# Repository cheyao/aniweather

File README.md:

<h1 align="center">Aniweather - Your personal anime weather station!</h1>

This is a 3D weather station! You can choose between displaying daily waifu pics and the current weather. **No external libraries used!**

Made for #asylum. The main API code is at https://github.com/cheyao/short with nest :D

To change the settings, edit `firmware/settings.h`! The weather info is mostly parsed on nest.

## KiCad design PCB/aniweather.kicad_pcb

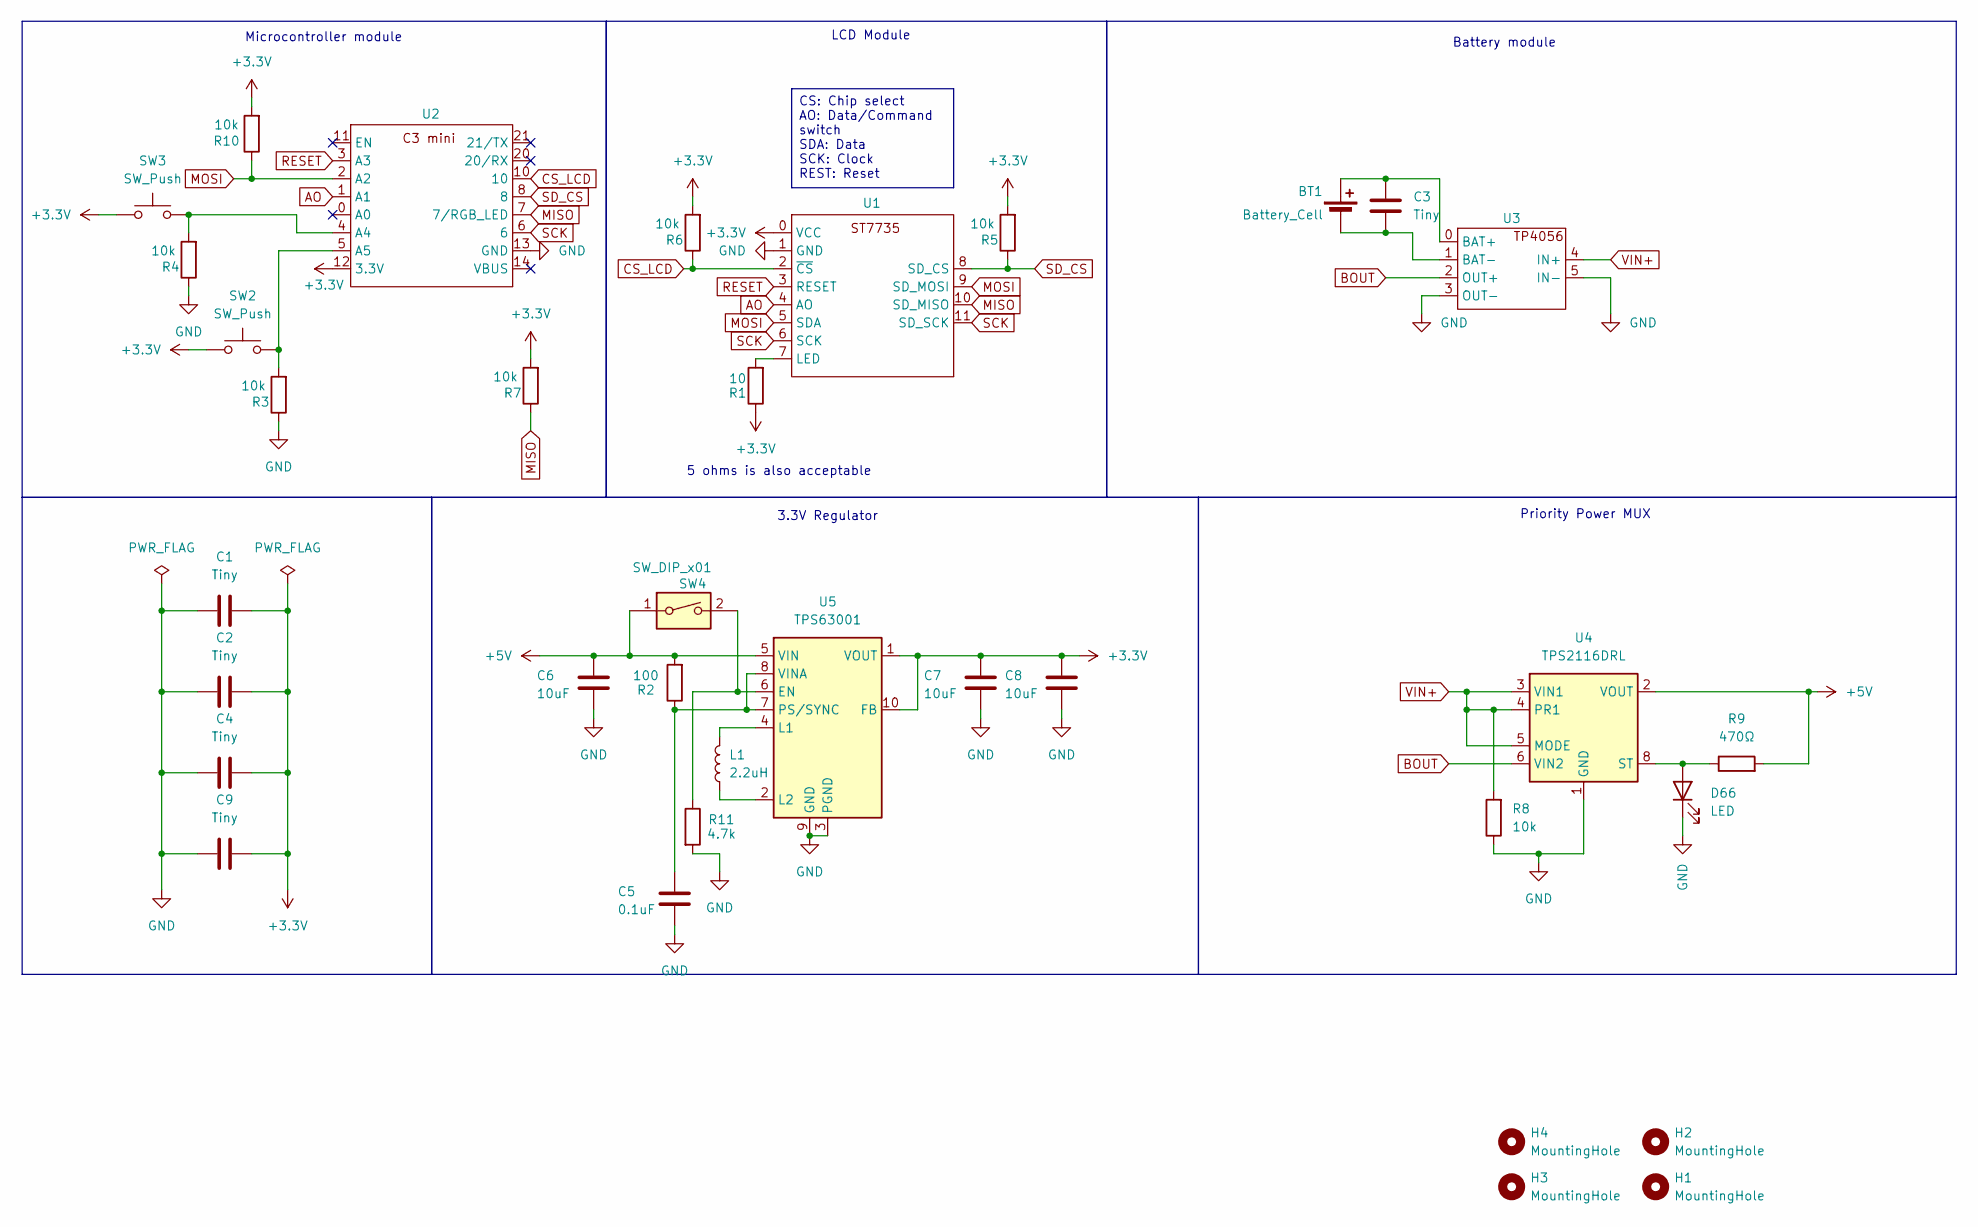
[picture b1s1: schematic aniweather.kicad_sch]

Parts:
BT1: Battery_Cell; TestPoint_2Pads_Pitch5.08mm_Drill1.3mm
C1, C2, C3, C4, C9: Tiny; C_0805_2012Metric_Pad1.18x1.45mm_HandSolder
C5: 0.1uF; C_0805_2012Metric_Pad1.18x1.45mm_HandSolder
C6, C7, C8: 10uF; C_0805_2012Metric_Pad1.18x1.45mm_HandSolder
D66: LED; LED_0603_1608Metric_Pad1.05x0.95mm_HandSolder
H1, H2, H3, H4: MountingHole; MountingHole_3.2mm_M3
L1: 2.2uH; NR3015T2R2M
R1: 10; R_0805_2012Metric_Pad1.20x1.40mm_HandSolder
R2: 100; R_0805_2012Metric_Pad1.20x1.40mm_HandSolder
R3, R4, R5, R6, R7, R8, R10: 10k; R_0805_2012Metric_Pad1.20x1.40mm_HandSolder
R9: 470Ω; R_0805_2012Metric_Pad1.20x1.40mm_HandSolder
R11: 4.7k; R_0805_2012Metric_Pad1.20x1.40mm_HandSolder
SW2, SW3: SW_Push; SW_PUSH_6mm
SW4: SW_DIP_x01; SW_DIP_SPSTx01_Slide_9.78x4.72mm_W7.62mm_P2.54mm
U1: ST7735
U2: WEMOS_C1_mini
U3: TP4056
U4: TPS2116DRL; SOT-583-8
U5: TPS63001; Texas_DRC0010J_ThermalVias

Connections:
+3.3V: C1.2, C2.2, C4.1, C7.1, C8.1, C9.1, R1.1, R5.2, R6.2, R7.2, R10.2, SW2.1, SW3.1, U1.0 (VCC), U2.12 (3.3V), U5.1 (VOUT), U5.10 (FB)
+5V: C6.1, R2.2, R9.2, SW4.1, U4.2 (VOUT), U4.7 (VOUT), U5.5 (VIN)
AO: U1.4 (AO), U2.1 (A1)
BOUT: U3.2 (OUT+), U4.6 (VIN2)
CS_LCD: R6.1, U1.2 (~CS), U2.10
GND: C1.1, C2.1, C4.2, C5.2, C6.2, C7.2, C8.2, C9.2, D66.1 (K), R3.1, R4.1, R8.1, R11.2, U1.1 (GND), U2.13 (GND), U3.3 (OUT-), U3.5 (IN-), U4.1 (GND), U5.3 (PGND), U5.9 (GND), U5.11 (PGND)
MISO: R7.1, U1.10 (SD_MISO), U2.7 (7/RGB_LED)
MOSI: R10.1, U1.5 (SDA), U1.9 (SD_MOSI), U2.2 (A2)
unnamed: BT1.1 (+), C3.1, U3.0 (BAT+)
unnamed: BT1.2 (-), C3.2, U3.1 (BAT-)
unnamed: D66.2 (A), R9.1, U4.8 (ST)
unnamed: R1.2, U1.7 (LED)
unnamed: R4.2, SW3.2, U2.4 (A4)
unnamed: R3.2, SW2.2, U2.5 (A5)
unnamed: R11.1, SW4.2, U5.6 (EN)
unnamed: L1.2, U5.4 (L1)
unnamed: L1.1, U5.2 (L2)
unnamed: C5.1, R2.1, U5.7 (PS/SYNC), U5.8 (VINA)
RESET: U1.3 (RESET), U2.3 (A3)
SCK: U1.6 (SCK), U1.11 (SD_SCK), U2.6
SD_CS: R5.1, U1.8 (SD_CS), U2.8
VIN+: R8.2, U3.4 (IN+), U4.3 (VIN1), U4.4 (PR1), U4.5 (MODE)

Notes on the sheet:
Microcontroller module
Battery module
3.3V Regulator
Priority Power MUX
5 ohms is also acceptable
LCD Module
CS: Chip select AO: Data/Command switch SDA: Data SCK: Clock REST: Reset

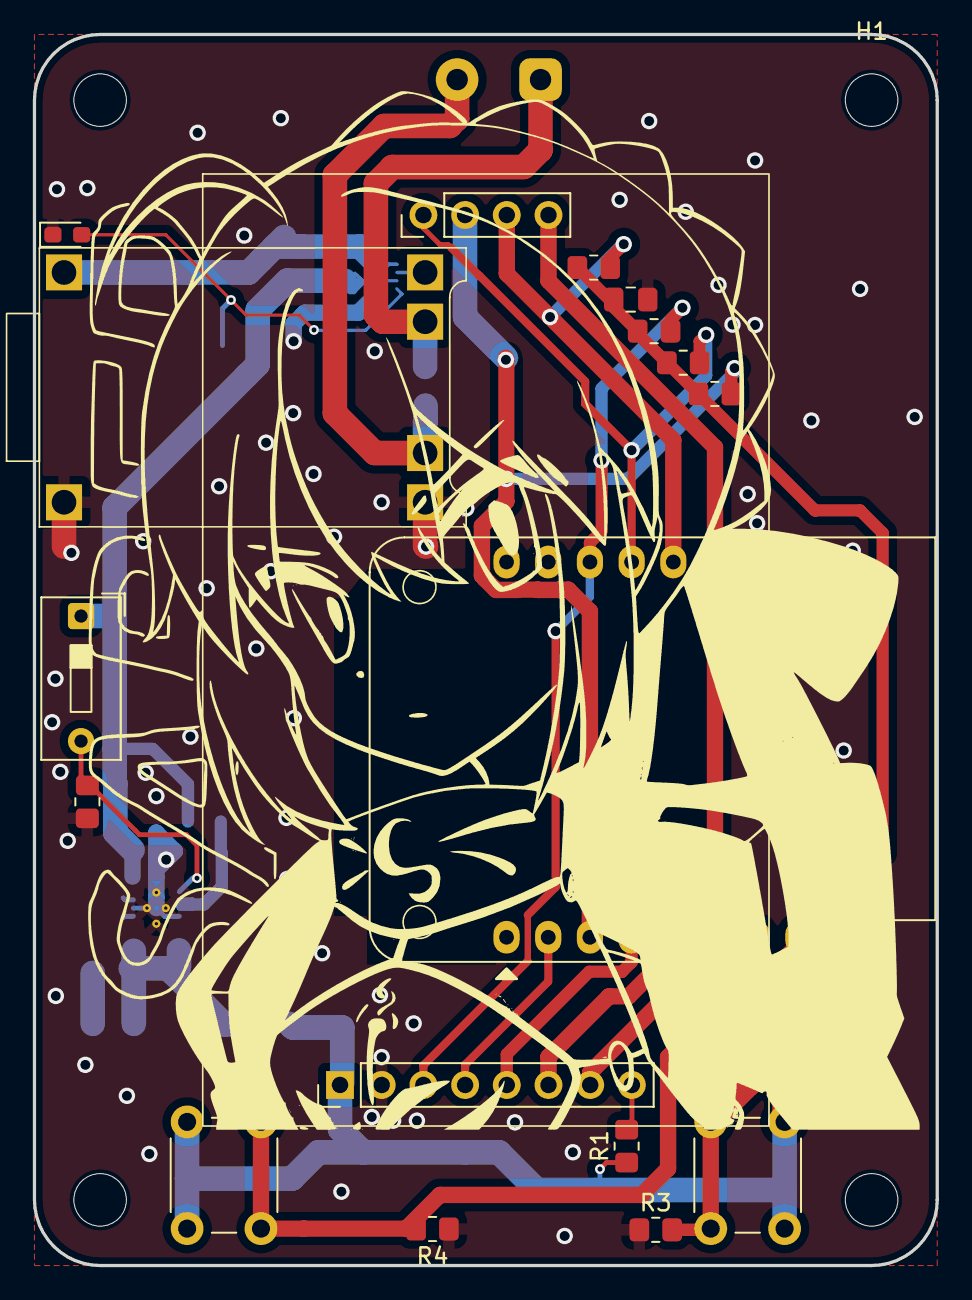
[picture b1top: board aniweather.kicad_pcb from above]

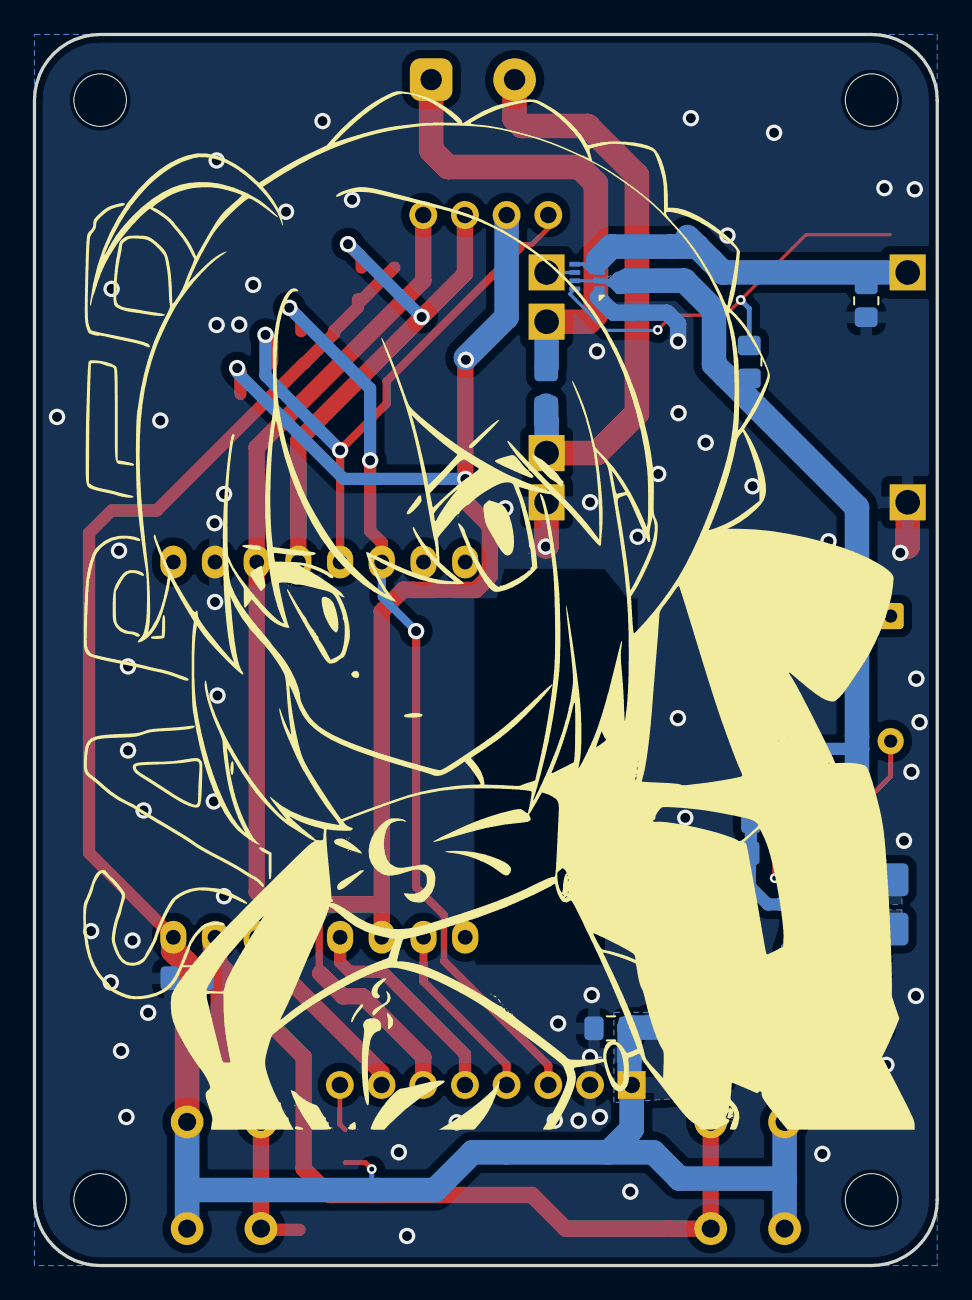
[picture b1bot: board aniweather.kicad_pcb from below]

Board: 2 copper layers, 55.0 x 75.0 mm, 37 parts (16 on the bottom side), 22 nets.

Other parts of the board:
G1, G2: LOGO

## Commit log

2024-12-03 Init
2024-12-05 Base board
2024-12-05 Further improvements
2024-12-07 Saber plus PCB start
2024-12-07 V1.0
2024-12-07 V1.0 rev 1
2024-12-08 Fix some small issues
2024-12-08 Bottom case
2024-12-09 Fix USB offset
2024-12-10 Case
2024-12-10 Rename
2024-12-10 Start of firmware
2024-12-11 Reroute board
2024-12-11 Round corner cases and button holes
2024-12-11 Revisions for PCB and start of the firmware
2024-12-12 Start of WIFI
2024-12-12 Multi-file
2024-12-12 Start of redo
2024-12-13 Time sync
2024-12-14 Finish firmware
2024-12-14 Final revision
2024-12-15 PCB revision
2024-12-15 I hope this is the final revision
2024-12-15 Add diode
2024-12-18 Hope last rev
2024-12-18 Really last rev
2024-12-19 Add diode to increase current capacity
2024-12-24 Readme and last rev
2024-12-26 Improve case detail
2025-01-23 Improve inductor footprint
2025-01-23 Improve readme
2025-02-26 Priority Power MUX
2025-03-01 FIX MISO and MOSI order
2025-04-01 Use SMD resistors
